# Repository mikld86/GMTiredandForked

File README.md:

<p align="center">

<br />

[![CC BY-NC-SA 4.0][cc-by-nc-sa-shield]][cc-by-nc-sa]
[![Sonar QG][sonar-shield]][sonar-url]
[![Sonar Violations][sonar-violations]][sonar-url]
[![Sonar Tech Debt][sonar-tech-debt]][sonar-url]

</p>

This project upgrades a Gaggia espresso machine with smart controls to improve your coffee-making experience. By adding a display and custom electronics, you can monitor and control the machine more easily.

## Features

- **Temperature Control**: Monitor the boiler temperature to ensure optimal brewing conditions.
- **Brew timer**: Set a target duration and run the brewing for the specific time.
- **Steam and Hot Water mode**: Control the pump and valve to run the respective task.
- **Safety Features**: Automatic shutoff if the system becomes unresponsive or overheats.
- **User Interface**: Simple, intuitive display to control and monitor the machine.

## Screenshots and Images

### Availability of kits

The group buy we did in 2024 is filled up but I'll keep the form open. You can register there to get notified about the second batch and from then on also general availability which is supposed to start in February 2025.

https://forms.gle/KEXdpgJGCZbsFdKD7

## How It Works

The display allows you to control the espresso machine and see live temperature updates. If the machine becomes unresponsive or the temperature goes too high, it will automatically turn off for safety.

## Docs

The docs were moved to [https://gaggimate.eu/](https://gaggimate.eu/). You can find all sourcing and assembly information there.

## License

This work is licensed under CC BY-NC-SA 4.0. To view a copy of this license, visit https://creativecommons.org/licenses/by-nc-sa/4.0/

[sonar-violations]: https://img.shields.io/sonar/blocker_violations/jniebuhr_gaggimate?server=https%3A%2F%2Fsonarcloud.io&style=for-the-badge
[sonar-shield]: https://img.shields.io/sonar/quality_gate/jniebuhr_gaggimate?server=https%3A%2F%2Fsonarcloud.io&style=for-the-badge
[sonar-tech-debt]: https://img.shields.io/sonar/tech_debt/jniebuhr_gaggimate?server=https%3A%2F%2Fsonarcloud.io&style=for-the-badge
[sonar-url]: https://sonarcloud.io/project/overview?id=jniebuhr_gaggimate
[cc-by-nc-sa]: http://creativecommons.org/licenses/by-nc-sa/4.0/
[cc-by-nc-sa-image]: https://licensebuttons.net/l/by-nc-sa/4.0/88x31.png
[cc-by-nc-sa-shield]: https://img.shields.io/badge/License-CC%20BY--NC--SA%204.0-lightgrey.svg?style=for-the-badge

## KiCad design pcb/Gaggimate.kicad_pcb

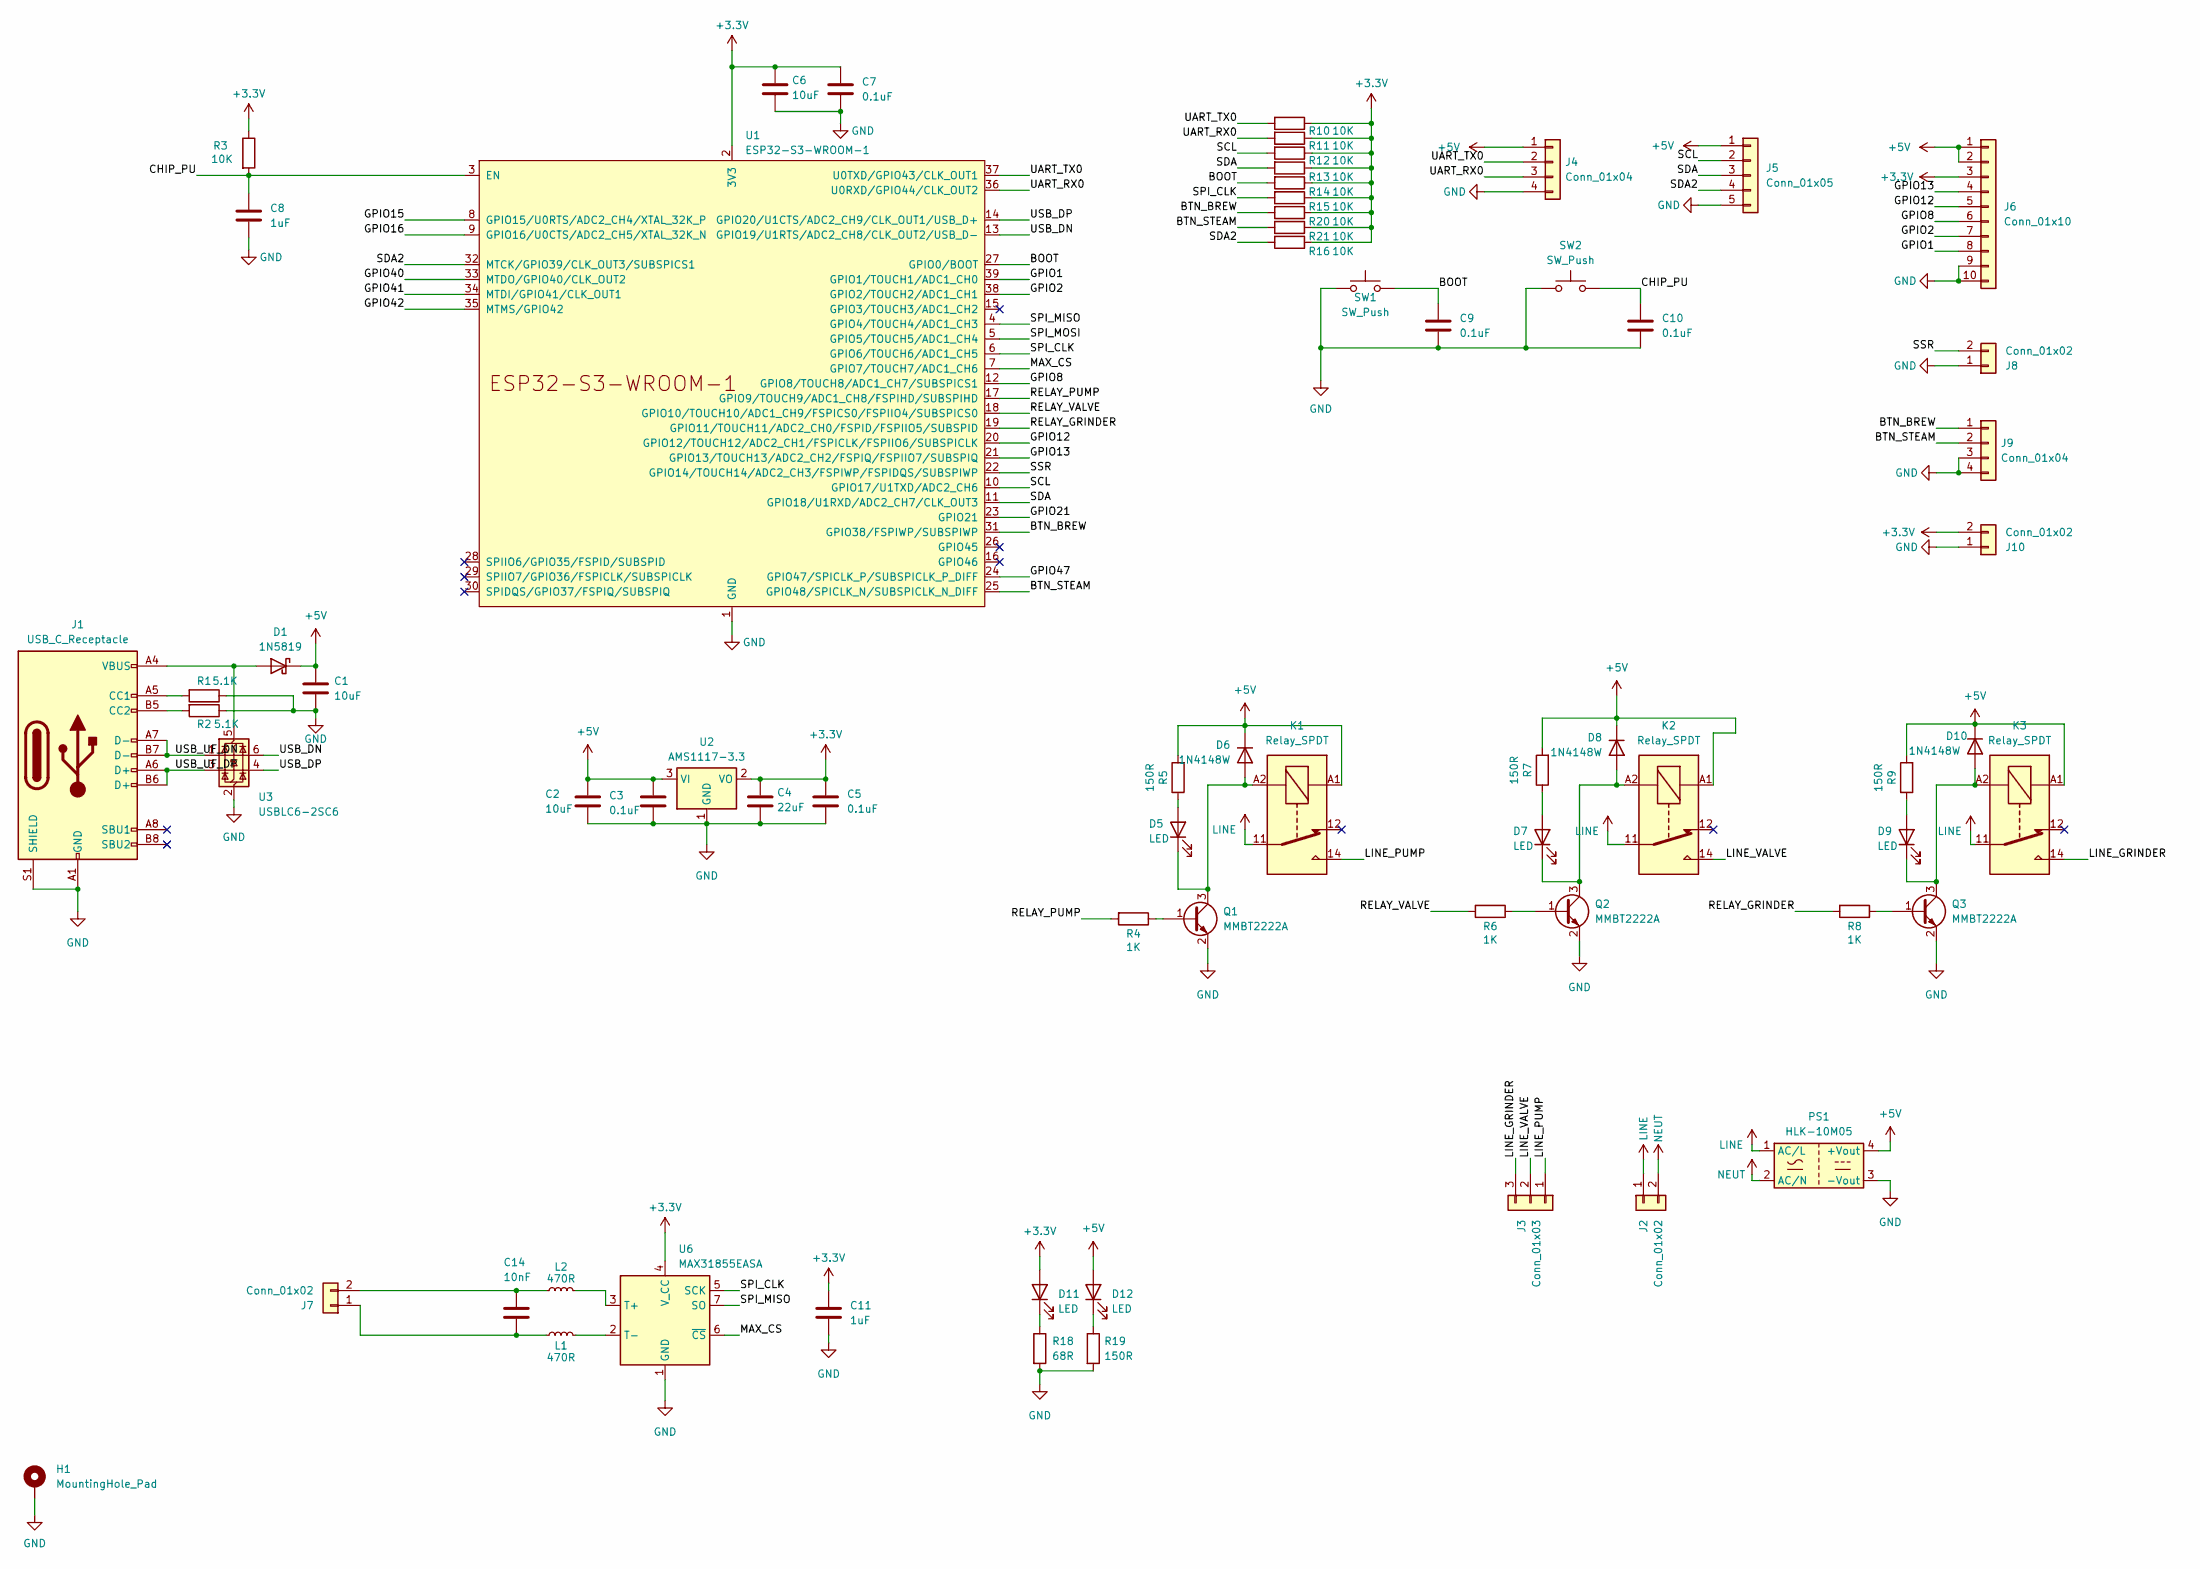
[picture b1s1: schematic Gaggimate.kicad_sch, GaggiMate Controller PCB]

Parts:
C1, C2, C6: 10uF; C_0805_2012Metric; LCSC C15850
C3, C5, C7, C9, C10: 0.1uF; C_0805_2012Metric; LCSC C49678
C4: 22uF; C_0805_2012Metric; LCSC C45783
C8, C11: 1uF; C_0805_2012Metric; LCSC C28323
C14: 10nF; C_0805_2012Metric; LCSC C1710
D1: 1N5819; D_SOD-123; LCSC C2891704
D5, D7, D9, D11, D12: LED; LED_0805_2012Metric; LCSC C84256
D6, D8, D10: 1N4148W; D_SOD-123; LCSC C81598
H1: MountingHole_Pad; MountingHole_3.2mm_M3_DIN965_Pad_TopBottom
J1: USB_C_Receptacle; USB_C_Receptacle_HRO_TYPE-C-31-M-12; LCSC C165948
J2: Conn_01x02; TerminalBlock_bornier-2_P5.08mm; LCSC C409161
J3: Conn_01x03; TerminalBlock_bornier-3_P5.08mm; LCSC C409163
J4: Conn_01x04; JST_XH_B4B-XH-A_1x04_P2.50mm_Vertical; LCSC C144395
J5: Conn_01x05; JST_XH_B5B-XH-A_1x05_P2.50mm_Vertical
J6: Conn_01x10; PinHeader_1x10_P2.54mm_Vertical; LCSC C5383117
J7: Conn_01x02; TerminalBlock_Phoenix_PT-1,5-2-3.5-H_1x02_P3.50mm_Horizontal; LCSC C415432
J8, J10: Conn_01x02; JST_XH_B2B-XH-A_1x02_P2.50mm_Vertical; LCSC C158012
J9: Conn_01x04; JST_XH_B4B-XH-A_1x04_P2.50mm_Vertical
K1, K2, K3: Relay_SPDT; Relay_SPDT_Finder_36.11; LCSC C35449
L1, L2: 470R; L_0603_1608Metric; LCSC C413961
PS1: HLK-10M05; Converter_ACDC_HiLink_HLK-10Mxx; LCSC C403745
Q1, Q2, Q3: MMBT2222A; SOT-23; LCSC C916372
R1, R2: 5.1K; R_0805_2012Metric; LCSC C27834
R3, R10, R11, R12, R13, R14, R15, R16, R20, R21: 10K; R_0805_2012Metric; LCSC C17414
R4, R6, R8: 1K; R_0805_2012Metric; LCSC C17513
R5, R7, R9, R19: 150R; R_0805_2012Metric; LCSC C17471
R18: 68R; R_0805_2012Metric; LCSC C17802
SW1, SW2: SW_Push; SW_SPST_SKQG_WithStem; LCSC C116647
U1: ESP32-S3-WROOM-1; LCSC C2913201
U2: AMS1117-3.3; SOT-223-3_TabPin2; LCSC C6186
U3: USBLC6-2SC6; SOT-23-6; LCSC C2827654
U6: MAX31855EASA; SOIC-8_3.9x4.9mm_P1.27mm; LCSC C52028

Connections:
+3.3V: C4.1, C5.1, C6.1, C7.1, C11.1, D11.2 (A), J6.3, J10.2, R3.1, R10.1, R11.1, R12.1, R13.1, R14.1, R15.1, R16.1, R20.1, R21.1, U1.2 (3V3), U2.2 (VO), U6.4 (V_CC)
+5V: C1.1, C2.1, C3.1, D1.1 (K), D6.1 (K), D8.1 (K), D10.1 (K), D12.2 (A), J4.1, J5.1, J6.1, J6.2, K1.A1, K2.A1, K3.A1, PS1.4 (+Vout), R5.2, R7.2, R9.2, U2.3 (VI)
/BOOT: C9.1, R14.2, SW1.2, U1.27 (GPIO0/BOOT)
/BTN_BREW: J9.1, R20.2, U1.31 (GPIO38/FSPIWP/SUBSPIWP)
/BTN_STEAM: J9.2, R21.2, U1.25 (GPIO48/SPICLK_N/SUBSPICLK_N_DIFF)
/CHIP_PU: C8.1, C10.1, R3.2, SW2.2, U1.3 (EN)
/GPIO1: J6.8, U1.39 (GPIO1/TOUCH1/ADC1_CH0)
/GPIO2: J6.7, U1.38 (GPIO2/TOUCH2/ADC1_CH1)
/GPIO8: J6.6, U1.12 (GPIO8/TOUCH8/ADC1_CH7/SUBSPICS1)
/GPIO12: J6.5, U1.20 (GPIO12/TOUCH12/ADC2_CH1/FSPICLK/FSPIIO6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)
/GPIO13: J6.4, U1.21 (GPIO13/TOUCH13/ADC2_CH2/FSPIQ/FSPIIO7/S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)
/GPIO15: U1.8 (GPIO15/U0RTS/ADC2_CH4/XTAL_32K_P)
/GPIO16: U1.9 (GPIO16/U0CTS/ADC2_CH5/XTAL_32K_N)
/GPIO21: U1.23 (GPIO21)
/GPIO40: U1.33 (MTDO/GPIO40/CLK_OUT2)
/GPIO41: U1.34 (MTDI/GPIO41/CLK_OUT1)
/GPIO42: U1.35 (MTMS/GPIO42)
/GPIO47: U1.24 (GPIO47/SPICLK_P/SUBSPICLK_P_DIFF)
/LINE_GRINDER: J3.3, K3.14
/LINE_PUMP: J3.1, K1.14
/LINE_VALVE: J3.2, K2.14
/MAX_CS: U1.7 (GPIO7/TOUCH7/ADC1_CH6), U6.6 (~CS)
/RELAY_GRINDER: R8.2, U1.19 (GPIO11/TOUCH11/ADC2_CH0/FSPID/FSPIIO5/S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)
/RELAY_PUMP: R4.2, U1.17 (GPIO9/TOUCH9/ADC1_CH8/FSPIHD/SUBSPIHD)
/RELAY_VALVE: R6.2, U1.18 (GPIO10/TOUCH10/ADC1_CH9/FSPICS0/FSPIIO4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)
/SCL: J5.2, R12.2, U1.10 (GPIO17/U1TXD/ADC2_CH6)
/SDA: J5.3, R13.2, U1.11 (GPIO18/U1RXD/ADC2_CH7/CLK_OUT3)
/SDA2: J5.4, R16.2, U1.32 (MTCK/GPIO39/CLK_OUT3/SUBSPICS1)
/SPI_CLK: R15.2, U1.6 (GPIO6/TOUCH6/ADC1_CH5), U6.5 (SCK)
/SPI_MISO: U1.4 (GPIO4/TOUCH4/ADC1_CH3), U6.7 (SO)
/SPI_MOSI: U1.5 (GPIO5/TOUCH5/ADC1_CH4)
/SSR: J8.2, U1.22 (GPIO14/TOUCH14/ADC2_CH3/FSPIWP/FSPIDQS/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)
/UART_RX0: J4.3, R11.2, U1.36 (U0RXD/GPIO44/CLK_OUT2)
/UART_TX0: J4.2, R10.2, U1.37 (U0TXD/GPIO43/CLK_OUT1)
/USB_DN: U1.13 (GPIO19/U1RTS/ADC2_CH8/CLK_OUT2/USB_D-), U3.6 (I/O1)
/USB_DP: U1.14 (GPIO20/U1CTS/ADC2_CH9/CLK_OUT1/USB_D+), U3.4 (I/O2)
/USB_UF_DN: J1.A7 (D-), J1.B7 (D-), U3.1 (I/O1)
/USB_UF_DP: J1.A6 (D+), J1.B6 (D+), U3.3 (I/O2)
GND: C1.2, C2.2, C3.2, C4.2, C5.2, C6.2, C7.2, C8.2, C9.2, C10.2, C11.2, H1.1, J1.A1 (GND), J1.A12 (GND), J1.B1 (GND), J1.B12 (GND), J1.S1 (SHIELD), J4.4, J5.5, J6.9, J6.10, J8.1, J9.3, J9.4, J10.1, PS1.3 (-Vout), Q1.2 (E), Q2.2 (E), Q3.2 (E), R1.1, R2.1, R18.2, R19.2, SW1.1, SW2.1, U1.1 (GND), U1.40 (GND), U1.41 (GND), U2.1 (GND), U3.2 (GND), U6.1 (GND); also elsewhere on the board
LINE: J2.1, K1.11, K2.11, K3.11, PS1.1 (AC/L)
NEUT: J2.2, PS1.2 (AC/N)
unnamed: D1.2 (A), J1.A4 (VBUS), J1.A9 (VBUS), J1.B4 (VBUS), J1.B9 (VBUS), U3.5 (VBUS)
unnamed: D5.2 (A), R5.1
unnamed: D5.1 (K), D6.2 (A), K1.A2, Q1.3 (C)
unnamed: D7.2 (A), R7.1
unnamed: D7.1 (K), D8.2 (A), K2.A2, Q2.3 (C)
unnamed: D9.2 (A), R9.1
unnamed: D9.1 (K), D10.2 (A), K3.A2, Q3.3 (C)
unnamed: D11.1 (K), R18.1
unnamed: D12.1 (K), R19.1
unnamed: J1.A5 (CC1), R1.2
unnamed: J1.B5 (CC2), R2.2
unnamed: C14.2, J7.1, L1.1
unnamed: C14.1, J7.2, L2.1
unnamed: Q1.1 (B), R4.1
unnamed: Q2.1 (B), R6.1
unnamed: Q3.1 (B), R8.1
unnamed: L2.2, U6.3 (T+)
unnamed: L1.2, U6.2 (T-)

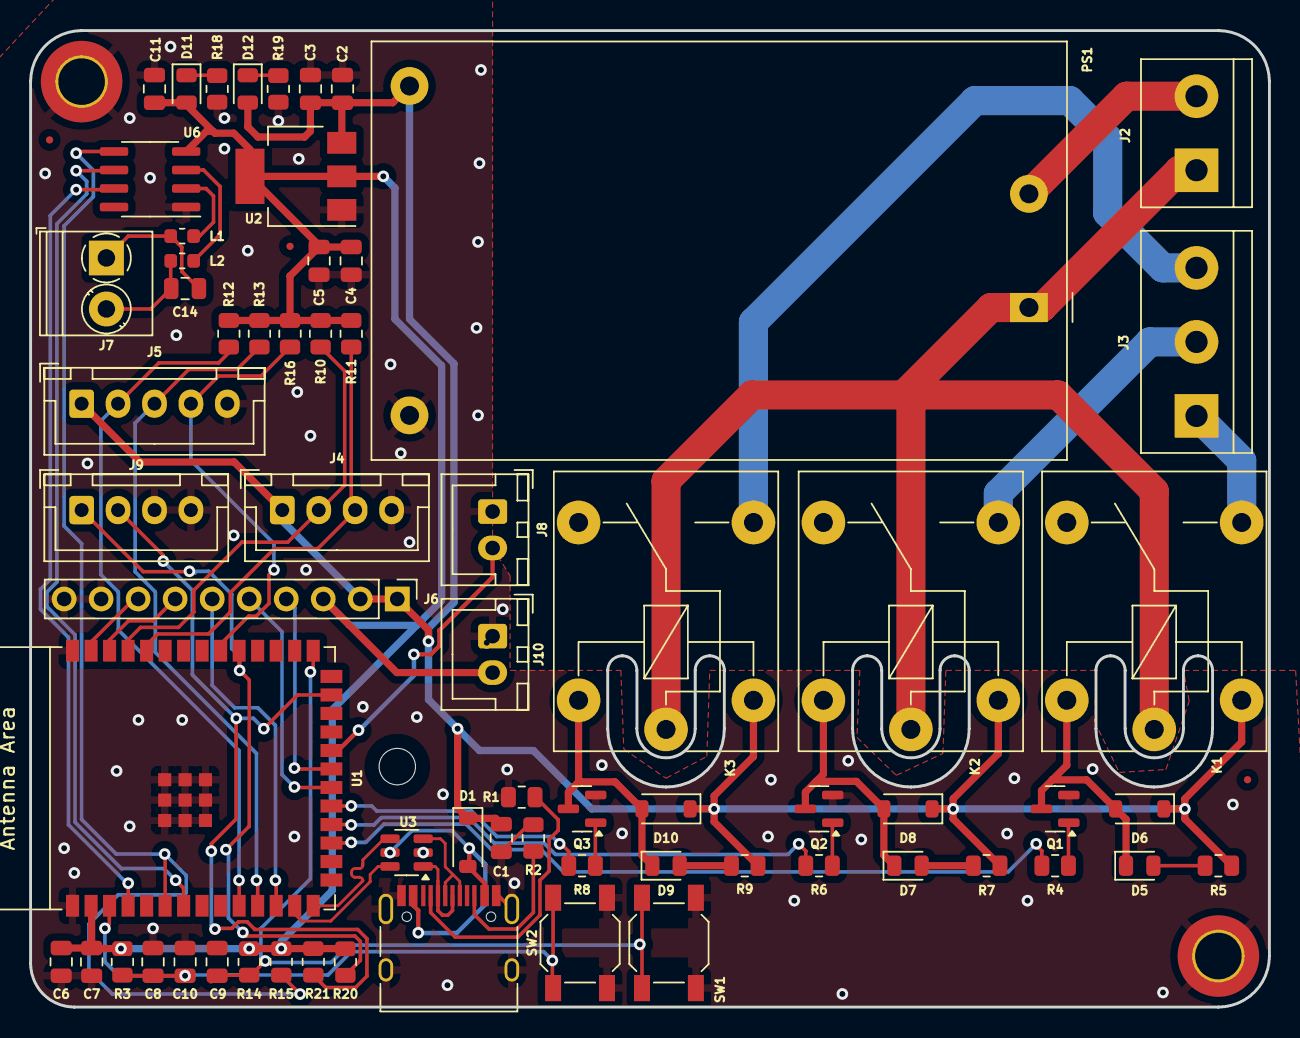
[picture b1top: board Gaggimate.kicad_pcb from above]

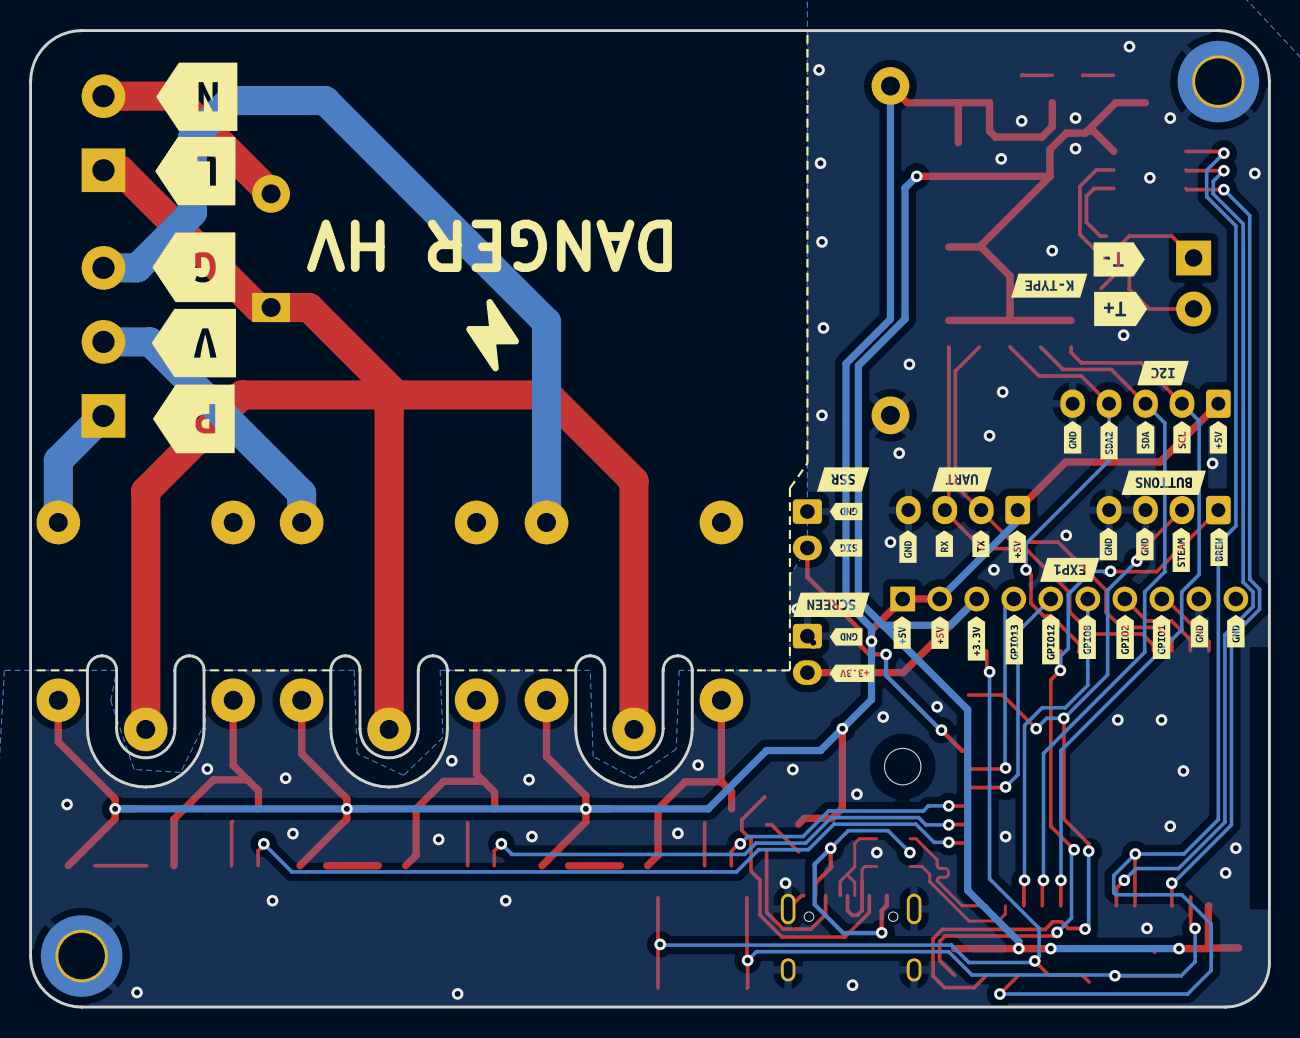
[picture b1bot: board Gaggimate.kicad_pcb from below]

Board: 2 copper layers, 85.0 x 67.0 mm, 109 parts (41 on the bottom side), 51 nets.

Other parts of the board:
H1#2: MountingHole_Pad; MountingHole_3.2mm_M3_DIN965_Pad_TopBottom
kibuzzard-6735A9F6: G***; kibuzzard-6735A9F6
kibuzzard-6735A9FB: G***; kibuzzard-6735A9FB
kibuzzard-67426AC2: G***; kibuzzard-67426AC2
kibuzzard-673226A0: G***; kibuzzard-673226A0
kibuzzard-673226A8: G***; kibuzzard-673226A8
kibuzzard-673226AF, kibuzzard-673226AF#2: G***; kibuzzard-673226AF
kibuzzard-673226B7: G***; kibuzzard-673226B7
kibuzzard-673226BE: G***; kibuzzard-673226BE
kibuzzard-673226D2: G***; kibuzzard-673226D2
kibuzzard-6732257B: G***; kibuzzard-6732257B
kibuzzard-6732261A: G***; kibuzzard-6732261A
kibuzzard-6732266F: G***; kibuzzard-6732266F
kibuzzard-6732270D: G***; kibuzzard-6732270D
kibuzzard-6732274F: G***; kibuzzard-6732274F
kibuzzard-6732277B: G***; kibuzzard-6732277B
kibuzzard-6732278E: G***; kibuzzard-6732278E
kibuzzard-6732279D: G***; kibuzzard-6732279D
kibuzzard-67322575: G***; kibuzzard-67322575
kibuzzard-67322649, kibuzzard-67322649#2, kibuzzard-67322649#3, kibuzzard-67322649#4, kibuzzard-67322649#5, kibuzzard-67322649#6, kibuzzard-67322649#7, kibuzzard-67322649#8: G***; kibuzzard-67322649
kibuzzard-67322650, kibuzzard-67322650#2, kibuzzard-67322650#3, kibuzzard-67322650#4: G***; kibuzzard-67322650
kibuzzard-67322655: G***; kibuzzard-67322655
kibuzzard-67322681: G***; kibuzzard-67322681
kibuzzard-67322686: G***; kibuzzard-67322686
kibuzzard-67322714: G***; kibuzzard-67322714
kibuzzard-67322749: G***; kibuzzard-67322749
kibuzzard-67322755: G***; kibuzzard-67322755
kibuzzard-67322768: G***; kibuzzard-67322768
kibuzzard-67322783: G***; kibuzzard-67322783
kibuzzard-67322796: G***; kibuzzard-67322796
kibuzzard-67322833: G***; kibuzzard-67322833

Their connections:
GND: H1#2.1; also elsewhere on the board

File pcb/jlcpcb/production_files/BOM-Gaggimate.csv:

Comment,Designator,Footprint,LCSC,Quantity
SW_Push,"SW1,SW2",SW_SPST_SKQG_WithStem,C116647,2
Conn_01x04,"J4,J9",JST_XH_B4B-XH-A_1x04_P2.50mm_Vertical,C144395,2
Conn_01x02,"J10,J8",JST_XH_B2B-XH-A_1x02_P2.50mm_Vertical,C158012,2
10uF,"C1,C2,C6",C_0805_2012Metric,C15850,3
USB_C_Receptacle,J1,USB_C_Receptacle_HRO_TYPE-C-31-M-12,C165948,1
10nF,C14,C_0805_2012Metric,C1710,1
10K,"R10,R11,R12,R13,R14,R15,R16,R20,R21,R3",R_0805_2012Metric,C17414,10
150R,"R19,R5,R7,R9",R_0805_2012Metric,C17471,4
1K,"R4,R6,R8",R_0805_2012Metric,C17513,3
68R,R18,R_0805_2012Metric,C17802,1
5.1K,"R1,R2",R_0805_2012Metric,C27834,2
USBLC6-2SC6,U3,SOT-23-6,C2827654,1
1uF,"C11,C8",C_0805_2012Metric,C28323,2
1N5819,D1,D_SOD-123,C2891704,1
ESP32-S3-WROOM-1,U1,ESP32-S3-WROOM-1,C2913201,1
Relay_SPDT,"K1,K2,K3",Relay_SPDT_Finder_36.11,C35449,3
HLK-10M05,PS1,Converter_ACDC_HiLink_HLK-10Mxx,C403745,1
Conn_01x02,J2,TerminalBlock_bornier-2_P5.08mm,C409161,1
Conn_01x03,J3,TerminalBlock_bornier-3_P5.08mm,C409163,1
470R,"L1,L2",L_0603_1608Metric,C413961,2
Conn_01x02,J7,"TerminalBlock_Phoenix_PT-1,5-2-3.5-H_1x02_P3.50mm_Horizontal",C415432,1
22uF,C4,C_0805_2012Metric,C45783,1
0.1uF,"C10,C3,C5,C7,C9",C_0805_2012Metric,C49678,5
MAX31855EASA,U6,SOIC-8_3.9x4.9mm_P1.27mm,C52028,1
Conn_01x10,J6,PinHeader_1x10_P2.54mm_Vertical,C5383117,1
AMS1117-3.3,U2,SOT-223-3_TabPin2,C6186,1
1N4148W,"D10,D6,D8",D_SOD-123,C81598,3
LED,"D11,D12,D5,D7,D9",LED_0805_2012Metric,C84256,5
MMBT2222A,"Q1,Q2,Q3",SOT-23,C916372,3
Conn_01x05,J5,JST_XH_B5B-XH-A_1x05_P2.50mm_Vertical,,1

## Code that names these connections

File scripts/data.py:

legend = [
    ("Ground", "gnd"),
    ("Power", "pwr"),
    ("PWM", "pwm"),
    ("AC", "ac"),
    ("Doc", "doc")
]

# Pinlabels

temp_sensor = [
    [
        ("T-", "temp"),
    ],
    [
        ("T+", "temp"),
    ],
]

uart = [
    [
        ("+5V", "pwr"),
    ],
    [
        ("TX", "comms"),
        ("gpio43", "doc"),
    ],
    [
        ("RX", "comms"),
        ("gpio44", "doc"),
    ],
    [
        ("GND", "gnd"),
    ],
]

i2c = [
    [
        ("+5V", "pwr"),
    ],
    [
        ("SCL", "comms"),
        ("gpio17", "doc"),
    ],
    [
        ("SDA", "comms"),
        ("gpio18", "doc"),
    ],
    [
        ("GND", "gnd"),
    ],
]

buttons = [
    [
        ("Brew", "gpio"),
        ("gpio38", "doc"),
    ],
    [
        ("Steam", "gpio"),
        ("gpio39", "doc"),
    ],
    [
        ("GND", "gnd"),
    ],
    [
        ("GND", "gnd"),
    ],
]

ext = [
    [
        ("GND", "gnd"),
    ],
    [
        ("GND", "gnd"),
    ],
    [
        ("gpio1", "doc"),
    ],
    [
        ("gpio2", "doc"),
    ],
    [
        ("gpio8", "doc"),
    ],
    [
        ("gpio12", "doc"),
    ],
    [
        ("gpio13", "doc"),
    ],
    [
        ("+3.3V", "pwr"),
    ],
    [
        ("+5V", "pwr"),
    ],
    [
        ("+5V", "pwr"),
    ],
]

screen = [
    [
        ("GND", "gnd"),
        ("Screen", "doc"),
    ],
    [
        ("+3.3V", "pwr"),
        ("Screen", "doc"),
    ],
]

ssr = [
    [
        ("GND", "gnd"),
    ],
    [
        ("SSR", "pwm"),
        ("gpio14", "doc"),
    ],
]

ac_in = [
    [
        ("N", "ac"),
    ],
    [
        ("L", "ac"),
    ],
]

relais_out = [
    [
        ("Grinder", "ac"),
        ("gpio11", "doc"),
    ],
    [
        ("Valve", "ac"),
        ("gpio10", "doc"),
    ],
    [
        ("Pump", "ac"),
        ("gpio9", "doc"),
    ],
]

annotation_usb = ["USB-C", "port"]
annotation_btn_boot = ["BOOT", "button"]
annotation_btn_reset = ["EN", "button"]

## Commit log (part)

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2024-11-06 fix: Add montserrat web font
2024-11-07 chore: Move lilygo code to separate folder, cleanup comments
2024-11-07 fix: Conditionally enable homekit
2024-11-08 feat: Shift around a lot of code, put values into Settings class with automatic saving
2024-11-08 fix: add clang-tidy fix
2024-11-16 feat: Add machine render to README
2024-11-18 feat: Add new STLs
2024-11-20 feat: Add adjustments to PCB, pcb diff pipeline
2024-11-20 Create CNAME
2024-11-20 feat: Remove docs from main repo
2024-11-20 fix: Remove static workflow from main repo
2024-11-21 chore: Regenerate pinout
2024-11-21 fix: Fix favicon and host
2024-11-22 feat: Replace 10uF output capacitor with 22uF
2024-11-24 feat: Move MAX31885, add SDA2, add silkscreen adjustments
2024-11-24 fix: Exchange switch for correct model
2024-11-24 fix: Retract ground plane a bit
2024-11-26 chore: Fix sonarqube issues #1
2024-11-26 chore: Fix sonarqube issues #3
2024-11-26 feat: Add CAD files for PCB case and screen
2024-11-27 fix: Fix sonarqube errors
2024-11-27 feat: Make display part of OTA work
2024-11-27 fix: Fix style css
2024-11-28 fix: Fix temp live update
2024-12-02 fix: Simplify OTA
2024-12-02 fix: Fix pinout diagram for new PCB layout
2024-12-03 fix: Fix analog frequency
2024-12-11 feat: Use single origin icons, change arc
2024-12-11 feat: Add new screens
2024-12-17 fix: Remove slow animations, fix lvgl settings, fix slow AP mode
2024-12-19 fix: Fix workflow
2024-12-19 feat: Add OTA improvements, BLE OTA receiver code
2024-12-19 fix: Fix display build with BLE ota
2024-12-26 Added variant without screwholes
    This screen backplate model fits the GCP better, by having magnets placed lower. This is a version without screw holes.
2025-01-10 feat: Add angled screen case
2025-01-11 fix: Ignore data files
2025-01-11 feat: Use flex for menu, unload screens
2025-01-12 feat: Add brew screen logic for volumetric brewing
2025-01-12 chore: Reformat
2025-01-14 feat: Rework UI, add waveshare driver, add BLE preparation
2025-01-17 fix: Add working waveshare 2.8 inch driver
2025-01-18 feat: Allow skipping preinfusion
2025-01-18 fix: Fix formatting
2025-01-20 fix: Clean up brew phase code
2025-01-25 fix: Fix pid bug with temp offset
2025-01-30 fix: Fix double call to target volume
2025-01-30 feat: Set mode to brew on menu
    Fixes #47
2025-01-30 feat: Add homekit setup instructions Fixes #54
2025-01-31 feat: Add grind by weight
2025-02-01 feat: Keep last process
2025-02-01 fix: Raise predictive time
2025-02-01 fix: Revert proxy hostname
2025-02-01 Aading mqtt user and password
    WIP
2025-02-01 Changed text for mqtt fields
2025-02-01 fix: Remove code duplication
2025-02-01 feat: Enable captive portal for AP mode\nFixes #83
2025-02-04 feat: Upgrade expansion template to IO extender version
2025-02-04 feat: Throttle temperature updates by only publishing actual changes
2025-02-05 chore: Format web code
2025-02-05 feat: Add brew overview
2025-02-05 fix: Fix grind predictive scales
2025-02-11 fix: Cleanup before board v2
2025-02-15 Changes to brew start and end mqtt topic
2025-03-09 feat: Add felicita arc, fix Eureka scales
2025-03-11 feat: Add varia, decent scales
2025-03-15 feat: Start reworking controller code, move it into sub-project (#46)
    * feat: Start reworking controller code, move it into sub-project
    * feat: Add board autodetection
    * chore: Fix build, format
    * feat: Add new board version
2025-03-16 fix: Add nightly version to build (#144)
2025-03-16 fix: Fetch tags in build
2025-03-16 fix: Add version.txt to output
2025-03-16 feat: Raise weight output limit to 250 (#149)
    Fixes #138
2025-03-17 fix: Fix captive portal (#152)
    * fix: Fix captive portal
    * fix: Remove unused HTML
2025-03-18 fix: Raise delay between OTA messages
2025-03-19 fix: Add LPF for heater
2025-03-19 fix: Fix heater, add debug logging
2025-04-01 Fixed indent
    Fixed indent
2025-04-01 feat: Automatically run autotune on machine startup (#167)
    * feat: Automatically startup heater in autotune mode
    * fix: Fix board value
2025-04-01 fix: Switch back to PID loop
2025-04-06 feat: Fix pressing through wakeup, adjust button borders (#170)
2025-04-06 feat: Make standby timeout configurable (#172)
    Fixes #120
2025-04-15 fix: Fix some bugs
2025-05-01 fix: Fix dark mode display of web ui (#182)
2025-05-19 fix: Fix PID heater
2025-05-22 fix: Fix standby timeout
2025-05-24 fix: Fix spiffs layout
2025-06-03 feat: Try out Nayrods PID library (#223)
    * feat: Try out Nimrod PID library
    * fix: Rename PID lib
    * feat: Publish artifacts to GH-pages
    * fix: Fix PR workflow
    * fix: Fix case
    * feat: Add required confirmations as controllable
2025-06-03 fix: Add some more info and safety to new autotune
2025-06-06 feat: Introduce profiles (#175)
    * feat: Add profile edit screen
    * fix: Fix merge errors
    * feat: Add new profile screen
    * fix: Fix PID heater
    * feat: Add profile progress
    * feat: Repair code after cherrypicking, finish touch ui, add migration
2025-06-06 fix: Add improved pump control
2025-06-06 chore: ignore local config
2025-06-06 fix: Fix null division bugs
2025-06-13 fix: Swap out PSM library
2025-06-13 feat: Add styled tooltips
2025-06-13 Revert "fix: Shrink bundle size by 6x"
    This reverts commit c95f2395d2db938e4e002d05a7aa92eb9e94a7c8.
2025-06-14 Add Clock format to settings and UI (#246)
2025-06-15 feat: Add flush feature (#247)
2025-06-15 feat: Add export for settings and all profiles
2025-06-16 fix: Fine-tune new pump library
2025-06-27 Feature/standby brightness reduction (#266)
    * cpp side impl
    * webui side
    * Fix bad unstash
    * Add zero standby brightness
    * Claude to include a toggle
    * Move standby brightness handling to updateStandbyScreen
2025-06-27 Allowing any float value for the auto adjust brew and grind delay values. (#265)
2025-06-29 feat: Steam Rework and temperature indicator (#277)
    * feat: Redesign UI for new steam mode
    * Make it green (when ready) (#272)
    * feat: Add UI Changes
    * feat: Make steam pump percentage adjustable
    * feat: Change button control for steam mode
    * feat: Major UI speedup, add auto steam
2025-06-30 fix: Update asynctcp, fix websocket reconnect
2025-06-30 fix: Hide wifi password in AP mode
    Fixes #257
2025-06-30 fix: Autoconnect scale when startup mode is brew (#280)
2025-07-04 Remove old NayrodPID lib to add as submodule
2025-07-06 Convert submodule into regular directory
2025-07-09 get pump cmd for flow control
2025-07-09 fix: Remove unused wifi manager
2025-07-09 fix: Control text wrap mode for user programmable fields (#295)
2025-07-09 fix: Fix wrong flow when no brew is running
2025-07-10 fix: Initialize wifi last
2025-07-10 fix: Fix too verbose logging
2025-07-11 fix: Replace wifi manager
2025-07-13 fix: Improve heater safeguards (#304)
2025-07-13 feat: Revert wifi manager, use simple wifi
2025-07-14 fix: Use log tag in controller
2025-07-14 fix: Fix include
2025-07-16 Changed ESP_PANEL_LCD_RGB_TIMING_FREQ_HZ (#306)
    * Update BLEScalePlugin.cpp for WeighMyBru Scale Support
    * Added WeighMyBru Scale Support & Updated platformio.ini
    * Add GitHub Pages firmware flasher
    * Fixed URL for flashing
    * Auto-update firmware files [skip ci]
    * Auto-update firmware files [skip ci]
2025-07-17 Move Save Preferences button on OTA page and fix overflow issues (#305)
    * move "Save preferences" button on OTA page, fix overflow issues on OTA and Settings page
    The only real changes are to /web/src/pages/OTA/index.jsx and /web/src/pages/Settings/index.jsx, the rest are from running the prettier command
    Moved the "Save preferences" button to the div containing the Update channel selector to clarify that the button saves the update channel chosen
    Added flex-wrap and gap-y-2 to the div containing the Update-buttons to allow the buttons to stack vertically when there is not enough width to stack them horizontally
    * change flex gap to gap-y-1 on container for Update-buttons to match gap be
2025-07-23 Tailwind and Vite upgrade (#318)
    * update vite
    * Upgrade TailwindCSS and Vite
    Upgraded to Tailwind v4
    Upgraded to Vite v7
    Removed PostCSS as its no longer required by tailwind
    updated styles to conform to tailwind requirements not totally sure what you want on the border as border-opacity is depreciated
2025-07-23 fix: Add back smoothing in pressure controller (#319)
2025-07-26 feat: Allow flow control with pressure limit (#320)
    * feat: Allow flow control with pressure limit
    * fix: Cleanup unused code
    * feat: Allow controlling flow from profile
    * fix: Add codereview feedback
    * fix: Fix unused variable
    * fix: Fix flow control to use pump not puck flow
2025-07-26 Fixed PSM divider back to 2 (#323)
2025-07-27 Implement support for 1.43 inch LilyGo T-Display S3 AMOLED (DS) (#218)
    * Add the board
    * Basic Panel, Drivers and LVGL support
    * True black for amoled
    * BLE mocks until I get the controller board
    * Add rotation to T-Display
    * Add sleep/wakeup routines
2025-07-28 feat: Add headless version (#335)
    * feat: Add headless web ui
    * feat: Add separate platformio env
    * feat: Add headless build
2025-07-28 feat: Add back button to profile edit
2025-07-30 feat: Add sunrise (#338)
2025-08-03 feat: Make shoestringquartet happy
2025-08-12 fix: Debug steam flow
2025-08-12 fix: Fix reset logic for Waveshare 2.1 screen
2025-08-12 fix: Fix waveshare screen dimming
2025-08-13 Daisy UI Migration (#355)
    * Add Daisy Ui (#339)
    * Initial Daisy Ui transition and 4 themes to start
    * Update Ui
    * Fix SonarCloud issues
    * Remove Computed Single line Chart Register
    * Use JSX syntax
2025-08-13 fix: Fix momentary buttonsg
2025-08-15 Add Flush to WebUI (#360)
    * Add Flush to WebUI
    * Pass isFlushing as a prop
    * Make flush button smaller and bellow brew button
    ---------
2025-08-17 Add advanced profiles (#365)
    * feat: Add schema changes for advanced profiles
    * feat: Add exit conditions and temperature profiling
    * feat: Separate process classes
    * chore: Reformat
    * feat: Add transitions
    * fix: Add code review feedback
2025-08-17 fix: Fix phase temperature
2025-08-18 fix: Fix tcl import, fix chart
2025-08-20 fix: Fix tcl converter bug
2025-08-21 fix: Switch NTP logic
2025-08-21 fix: Fix compile warnings
2025-08-21 feat: Add experimental outputs for flow estimation
2025-08-21 fix: Optimize loading of profile selection
2025-08-21 Fix json import/export on Android (#366)
2025-08-21 feat: add mqtt auto discovery (#220)
    * add mqtt device discover to HA
    * get versions from controller
    * round temperature values
    * add Home Assistant topic on settings
    * add haTopic to api handler
    * add input field on settings page
2025-08-22 Nayrod experimental (#376)
    * Update NayrodLab with lab equipment
    * Flow and coffee output estimation improvement. First drop synch
2025-08-22 Add move up/down functionality and persist profile order (#377)
    * Add move up/down functionality for profile cards
    * Persist reordering of profiles
    * Fix PR comments
    * Minor cleanup in Settings.cpp
    Makes the code a bit easier to read.
    * Add aria-disabled to move-buttons.
2025-08-22 Return ordered favorites based on stored profile order (#381)
    * Update getFavoritedProfiles to return ordered favorites based on stored profile order
    * PR comments fix
    * Fix PR comment
2025-08-22 feat: Allow steam pump cutoff to be configurable
2025-08-23 fix: Skip PWM logic for 0/100 setting of simple pump
2025-08-23 fix: Fix formatting of steam pump percentage field
2025-08-24 fix: Fix add target bug in some browsers
2025-08-25 fix: Allow to change adaptive transition
2025-08-25 fix: Switch back to 250ms telemetry
2025-08-28 WifiManager v1.6.1: arm DHCP each retry; avoid radio power-off; fix precedence; disable sleep
2025-08-29 chore(wifi): remove all comments
2025-08-30 HomekitPlugin: auto-reset HomeKit identity on firmware change via HomeSpan CLI 'H' (uses BUILD_GIT_VERSION)
2025-09-03 wifi: register STA event handlers before WiFi.begin(); guard duplicate registration
